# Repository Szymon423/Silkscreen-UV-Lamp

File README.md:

<div align="center">

# Soldermask UV Lamp

**A tiny, USB-C powered UV lamp for curing UV soldermask on home-made PCBs.**
Plug it into any USB-C charger, put it over the board and let the UV LED harden the mask.

</div>

---

## Features

- **High-power UV LED.** Prolight Opto **PK2N-1KQE-SL** in a 1 W / 3 W package, with an optical lens on top to focus the light onto the board.
- **USB-C power.** 5.1 kΩ CC pull-downs, so it runs from any USB-C charger or power bank (C-to-C cables included). No buttons, no firmware – plug in and it's on.
- **Input protection.** TVS diode and a 10 µF bulk capacitor on VBUS.
- **Simple driver.** BC817 low-side transistor switch for the LED.
- **Configurable thermal pad.** Solder jumpers JP1–JP3 set how the LED's centre pad is connected (5 V / GND).
- **Built for heat.** Ø30 mm round PCB with an exposed copper pad and a dense via array to spread heat from the LED.
- **3D-printed enclosure.** Two parts screwed together by a thread, PCB held with two M2.5 screws.

## Gallery

<table>
  <tr>
    <td align="center" width="50%"><br><sub>Lens side</sub></td>
    <td align="center" width="50%"><br><sub>Inside, with the top part removed</sub></td>
  </tr>
  <tr>
    <td align="center"><br><sub>USB-C port</sub></td>
    <td align="center"><br><sub>Bottom</sub></td>
  </tr>
</table>

### PCB

<table>
  <tr>
    <td align="center" width="50%"><br><sub>LED side</sub></td>
    <td align="center" width="50%"><br><sub>USB-C and driver side</sub></td>
  </tr>
</table>

📄 **[Schematic (PDF)](docs/schematic.pdf)**

## Hardware overview

| Block | Part | Notes |
|---|---|---|
| UV LED | [Prolight Opto PK2N-1KQE-SL](https://www.tme.eu/pl/details/pk2n-1kqe-sl/diody-led-uv/prolight-opto/) | 1 W / 3 W package (`LED_1W_3W_R8` footprint) |
| Lens | [Citizen ILU-006-W](https://www.tme.eu/pl/details/ilu-006-w/soczewki/citizen-electronics/ilu-006-w-as/) | Focuses the beam onto the PCB |
| Driver | BC817 (SOT-23) | Low-side switch, 2.2 kΩ base resistor from VBUS |
| Power input | USB-C receptacle (GCT USB4105) | 5 V only, 2× 5.1 kΩ CC pull-downs |
| Protection | TVS diode (SMA) + 10 µF | On VBUS |
| PCB | Ø30 mm, round, 2 layers | Exposed copper + via array for cooling |

```
 USB-C (5 V) ──► TVS + 10 µF ──► UV LED (PK2N-1KQE-SL) ──► BC817 ──► GND
     │                                │                       ▲
     └── CC1/CC2: 5.1 kΩ to GND       └── JP1–JP3: LED pad    └── 2.2 kΩ from VBUS
```

## Repository structure

```
.
├── 01_Hardware/
│   ├── 01_KiCad/
│   │   ├── soldermask-uv-lamp/    # KiCad project (schematic + PCB)
│   │   │   └── production/        # Gerbers, BOM, pick & place
│   │   └── lib/                   # 3D models of the UV LED
│   └── 02_3D_Model/
│       ├── 3D-Printing/           # Enclosure STL files + print project (3MF)
│       └── model.blend            # Blender scene used for the renders
└── docs/                          # Images and schematic PDF for this README
```

> [!WARNING]
> This project is **work in progress**. Hardware v0.1 has not been fully tested yet, so order boards at your own risk.

> [!CAUTION]
> **UV light can damage your eyes and skin.** Never look into the LED while it is on, and use UV-blocking glasses.

## License

**Hardware** (schematics, PCB, enclosure, renders): [**CC BY-NC-SA 4.0**](LICENSE).
You may build, study and modify this design for **non-commercial** purposes, as long as you credit the author and share your changes under the same license.
**Selling boards, kits or devices based on this design is not allowed** without the author's written permission.

For commercial licensing, please get in touch.

---

<div align="center">
<sub>Designed by <b>Szymon Wąchała</b> · 2025–2026</sub>
</div>

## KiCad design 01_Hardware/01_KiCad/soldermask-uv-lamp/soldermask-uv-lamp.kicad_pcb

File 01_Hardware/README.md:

# Hardware | Soldermask UV Lamp

| Folder | Contents |
|---|---|
| [`01_KiCad/soldermask-uv-lamp`](01_KiCad/soldermask-uv-lamp) | KiCad 10 project: schematic and PCB |
| [`01_KiCad/soldermask-uv-lamp/production`](01_KiCad/soldermask-uv-lamp/production) | Fabrication output: Gerbers, BOM, pick & place |
| [`01_KiCad/lib`](01_KiCad/lib) | 3D models of the UV LED (Prolight PK2N-1KQE-SL) |
| [`02_3D_Model/3D-Printing`](02_3D_Model/3D-Printing) | Enclosure parts (`base.stl`, `top.stl`) and a ready print project (`.3mf`) |
| [`02_3D_Model/model.blend`](02_3D_Model) | Blender scene used for the renders |

A PDF of the schematic is in [`docs/schematic.pdf`](../docs/schematic.pdf).

Licensed under [CC BY-NC-SA 4.0](../LICENSE).

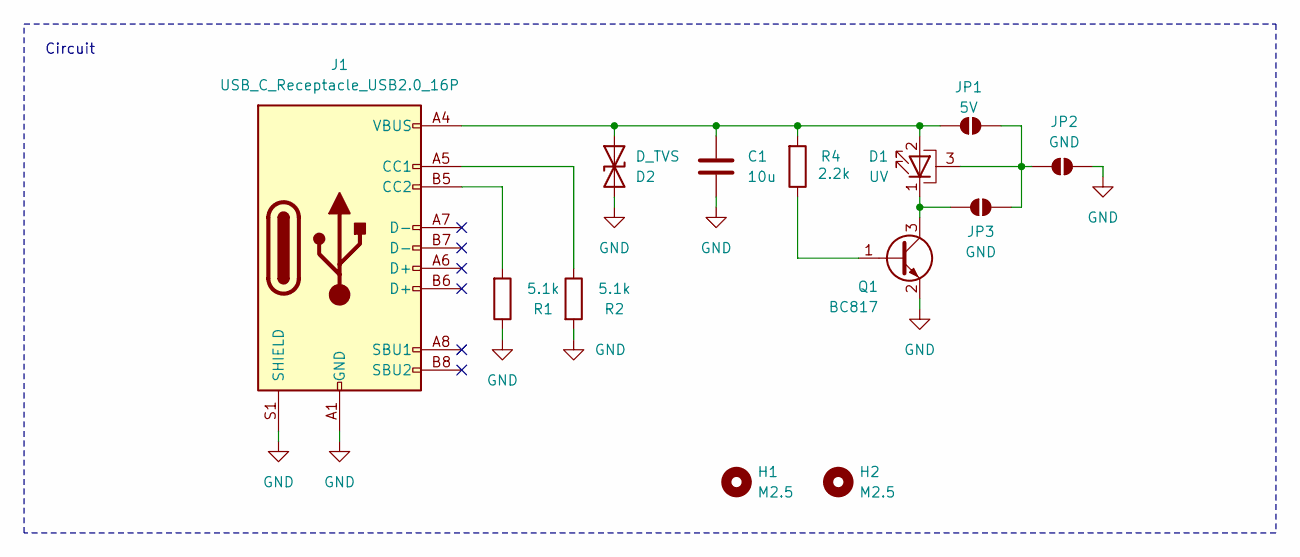
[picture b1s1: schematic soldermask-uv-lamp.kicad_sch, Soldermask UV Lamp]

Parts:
C1: 10u; C_1206_3216Metric
D1: UV; LED_1W_3W_R8
D2: D_TVS; D_SMA
H1, H2: M2.5; MountingHole_2.7mm_M2.5
J1: USB_C_Receptacle_USB2.0_16P; USB_C_Receptacle_GCT_USB4105-xx-A_16P_TopMnt_Horizontal
JP1: 5V; SolderJumper-2_P1.3mm_Open_RoundedPad1.0x1.5mm
JP2, JP3: GND; SolderJumper-2_P1.3mm_Open_RoundedPad1.0x1.5mm
Q1: BC817; SOT-23
R1, R2: 5.1k; R_0603_1608Metric
R4: 2.2k; R_0603_1608Metric

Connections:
GND: C1.2, D2.2 (A2), J1.A1 (GND), J1.A12 (GND), J1.B1 (GND), J1.B12 (GND), J1.S1 (SHIELD), JP2.1 (A), Q1.2 (E), R1.1, R2.2
unnamed: C1.1, D1.2 (A), D2.1 (A1), J1.A4 (VBUS), J1.A9 (VBUS), J1.B4 (VBUS), J1.B9 (VBUS), JP1.1 (A), R4.2
unnamed: D1.1 (K), JP3.1 (A), Q1.3 (C)
unnamed: D1.3 (PAD), JP1.2 (B), JP2.2 (B), JP3.2 (B)
unnamed: J1.A5 (CC1), R2.1
unnamed: J1.B5 (CC2), R1.2
unnamed: Q1.1 (B), R4.1

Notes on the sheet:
Circuit

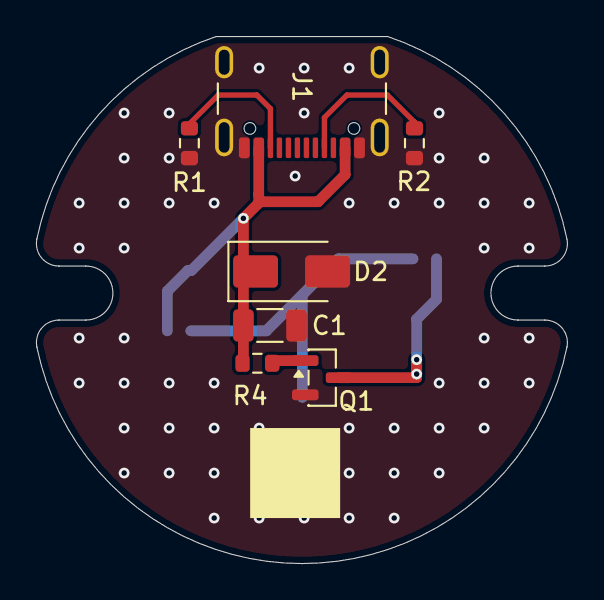
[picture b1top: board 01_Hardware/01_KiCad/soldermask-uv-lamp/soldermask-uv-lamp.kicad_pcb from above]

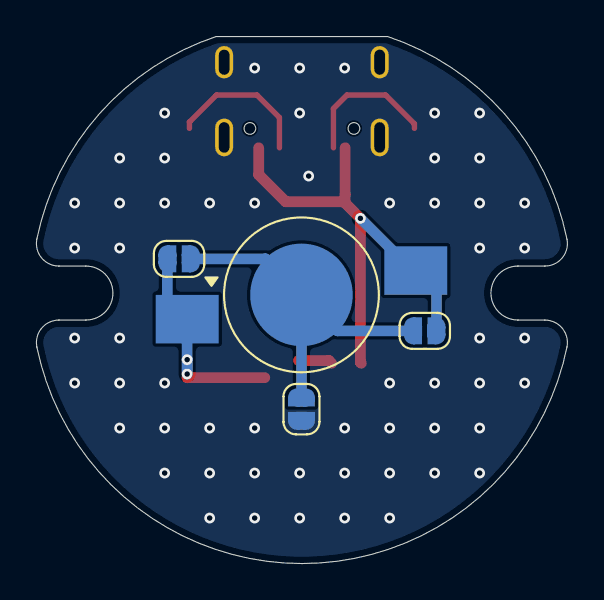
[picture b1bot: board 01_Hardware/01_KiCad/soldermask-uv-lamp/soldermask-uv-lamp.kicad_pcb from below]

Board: 2 copper layers, 29.5 x 29.3 mm, 13 parts (4 on the bottom side), 7 nets.

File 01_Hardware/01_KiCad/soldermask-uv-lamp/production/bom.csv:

Designator,Footprint,Quantity,Value,LCSC Part #
C1,1206,1,10u,
D1,LED_1W_3W_R8,1,UV,
D2,D_SMA,1,D_TVS,
J1,USB_C_Receptacle_GCT_USB4105-xx-A_16P_TopMnt_Horizontal,1,USB_C_Receptacle_USB2.0_16P,
Q1,SOT-23,1,BC817,
"R1, R2",0603,2,5.1k,
R4,0603,1,2.2k,

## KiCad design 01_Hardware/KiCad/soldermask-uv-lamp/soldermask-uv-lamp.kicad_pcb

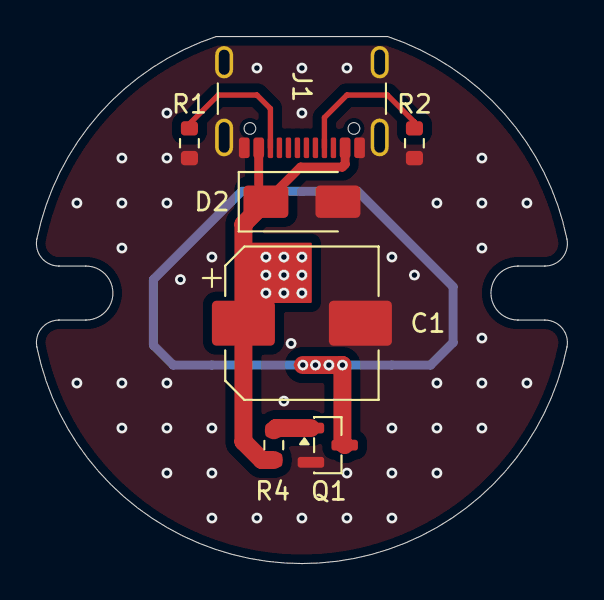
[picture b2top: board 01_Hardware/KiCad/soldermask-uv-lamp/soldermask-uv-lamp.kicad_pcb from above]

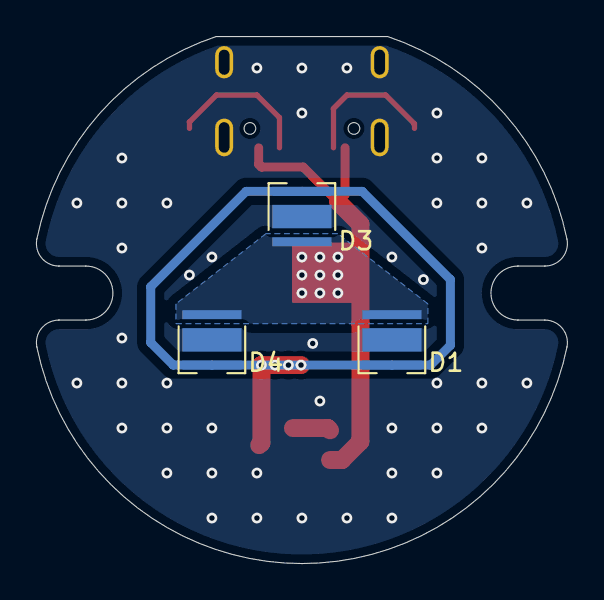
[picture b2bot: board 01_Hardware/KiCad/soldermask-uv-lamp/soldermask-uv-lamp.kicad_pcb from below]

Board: 2 copper layers, 29.5 x 29.3 mm, 10 parts (3 on the bottom side), 6 nets.

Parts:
C1: 470u; CP_Elec_8x10
D1, D3, D4: LED_Pad; LED_Cree-XHP35
D2: D_TVS; D_SMA
J1: USB_C_Receptacle_USB2.0_16P; USB_C_Receptacle_GCT_USB4105-xx-A_16P_TopMnt_Horizontal
Q1: BC817; SOT-23
R1, R2: 5.1k; R_0603_1608Metric
R4: 2.2k; R_0603_1608Metric

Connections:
5V: C1.1, D1.2 (A), D2.1 (A1), D3.2 (A), D4.2 (A), J1.A4 (VBUS), J1.A9 (VBUS), J1.B4 (VBUS), J1.B9 (VBUS), R4.1
GND: C1.2, D1.3 (PAD), D2.2 (A2), D3.3 (PAD), D4.3 (PAD), J1.A1 (GND), J1.A12 (GND), J1.B1 (GND), J1.B12 (GND), J1.S1 (SHIELD), Q1.2 (E), R1.2, R2.2
unnamed: D1.1 (K), D3.1 (K), D4.1 (K), Q1.3 (C)
unnamed: J1.A5 (CC1), R2.1
unnamed: J1.B5 (CC2), R1.1
unnamed: Q1.1 (B), R4.2

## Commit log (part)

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2025-11-21 Added captions to schematics and pcb design

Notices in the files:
README.md:
License: CC BY-NC-SA 4.0
